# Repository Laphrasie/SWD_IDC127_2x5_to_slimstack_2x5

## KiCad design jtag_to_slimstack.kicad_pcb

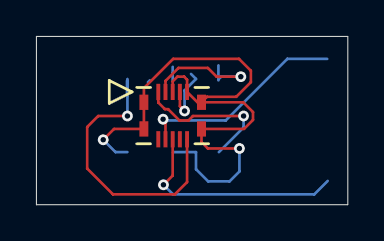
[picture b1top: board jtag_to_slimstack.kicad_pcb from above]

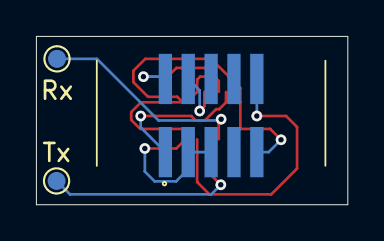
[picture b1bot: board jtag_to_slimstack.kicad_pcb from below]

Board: 2 copper layers, 17.3 x 9.3 mm, 4 parts (3 on the bottom side), 7 nets.

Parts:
J1: SHF-105-01-F-D-SM; SHF-105-01-X-D-SM
J3: 559099872; CON_559099872
Rx: UART Rx; TestPoint_Pad_D1.0mm
Tx: UART Tx; TestPoint_Pad_D1.0mm

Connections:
GND: J1.3 (GND), J1.5 (GND), J1.9 (GND), J3.3 (GND), J3.5 (GND), J3.P1 (GND), J3.P2 (GND), J3.P3 (GND), J3.P4 (GND)
unnamed: J1.10 (RSTN), J3.10 (RSTN)
unnamed: J1.4 (SWDCLK), J3.4 (SWCLK)
unnamed: J1.2 (SWDIO), J3.2 (SWDIO)
unnamed: J1.1 (VREF), J3.1 (VDD)
unnamed: J3.7 (UART_Rx), Rx.1
unnamed: J3.8 (UART_Tx), Tx.1

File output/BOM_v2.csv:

Id,Designator,Footprint,Quantity,Designation,Supplier,ref,Mouser ref,Mouser link
1,J3,CON_559099872,1,559099872,Molex,538-55909-9872,55909-9872,https://www.mouser.fr/ProductDetail/Molex/55909-9872?qs=iFVq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
2,J1,SHF-105-01-X-D-SM,1,SHF-105-01-F-D-SM,Samtec,SHF-105-01-F-D-SM,200-SHF10501FDSM,https://www.mouser.fr/ProductDetail/Samtec/SHF-105-01-F-D-SM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
